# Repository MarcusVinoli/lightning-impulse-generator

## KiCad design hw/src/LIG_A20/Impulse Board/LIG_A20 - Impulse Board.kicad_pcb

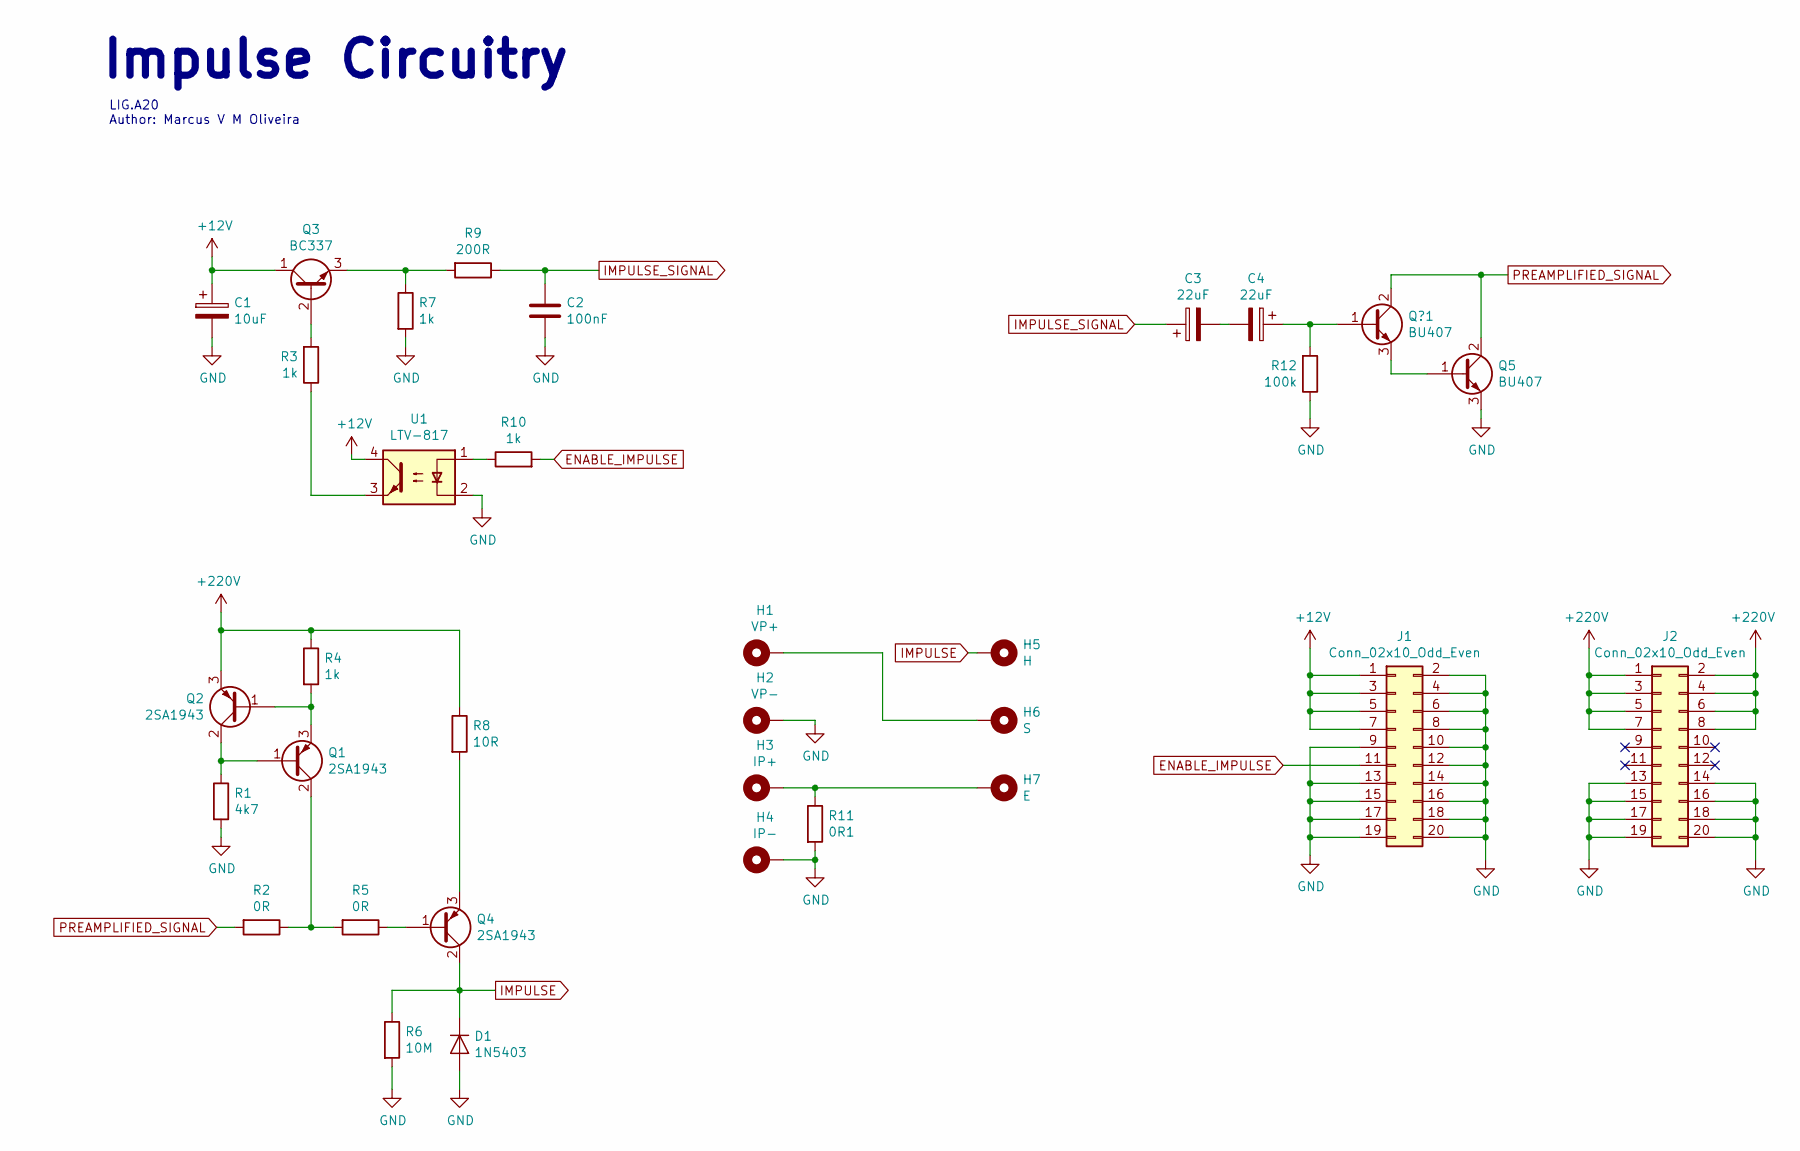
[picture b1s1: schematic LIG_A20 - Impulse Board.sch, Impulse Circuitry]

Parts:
C1: 10uF; CP_Radial_D4.0mm_P2.00mm
C2: 100nF; C_Disc_D5.1mm_W3.2mm_P5.00mm
C3, C4: 22uF; CP_Radial_D4.0mm_P2.00mm
D1: 1N5403; D_DO-201AD_P15.24mm_Horizontal
H1: VP+; MountingHole_2.7mm_M2.5_Pad
H2: VP-; MountingHole_2.7mm_M2.5_Pad
H3: IP+; MountingHole_2.7mm_M2.5_Pad
H4: IP-; MountingHole_2.7mm_M2.5_Pad
H5: H; MountingHole_2.7mm_M2.5_Pad
H6: S; MountingHole_2.7mm_M2.5_Pad
H7: E; MountingHole_2.7mm_M2.5_Pad
J1, J2: Conn_02x10_Odd_Even; PinHeader_2x10_P2.54mm_Vertical
Q1, Q2, Q4: 2SA1943; TO-264-3_Vertical
Q3: BC337; TO-92_Inline
Q5: BU407; TO-220-3_Vertical
Q?1: BU407; TO-220-3_Vertical
R1: 4k7; R_Axial_Power_L38.0mm_W9.0mm_P45.72mm
R2, R5: 0R; R_Axial_DIN0207_L6.3mm_D2.5mm_P10.16mm_Horizontal
R3, R4, R7, R10: 1k; R_Axial_DIN0207_L6.3mm_D2.5mm_P10.16mm_Horizontal
R6: 10M; R_Axial_DIN0207_L6.3mm_D2.5mm_P10.16mm_Horizontal
R8: 10R; R_Axial_Power_L38.0mm_W9.0mm_P45.72mm
R9: 200R; R_Axial_DIN0207_L6.3mm_D2.5mm_P10.16mm_Horizontal
R11: 0R1; R_Axial_DIN0918_L18.0mm_D9.0mm_P25.40mm_Horizontal
R12: 100k; R_Axial_DIN0207_L6.3mm_D2.5mm_P10.16mm_Horizontal
U1: LTV-817; DIP-4_W7.62mm

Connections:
+12V: C1.1, J1.1, J1.3, J1.5, J1.7, Q3.1 (C), U1.4
+220V: J2.1, J2.2, J2.3, J2.4, J2.5, J2.6, J2.7, J2.8, Q2.3 (E), R4.1, R8.1
ENABLE_IMPULSE: J1.11, R10.2
GND: C1.2, C2.2, D1.2 (A), H2.1, H4.1, J1.2, J1.4, J1.6, J1.8, J1.9, J1.10, J1.12, J1.13, J1.14, J1.15, J1.16, J1.17, J1.18, J1.19, J1.20, J2.13, J2.14, J2.15, J2.16, J2.17, J2.18, J2.19, J2.20, Q5.3 (E), R1.2, R6.2, R7.2, R11.2, R12.1, U1.2
IMPULSE: D1.1 (K), H5.1, Q4.2 (C), R6.1
IMPULSE_SIGNAL: C2.1, C3.1, R9.1
unnamed: C3.2, C4.2
unnamed: C4.1, Q?1.1 (B), R12.2
unnamed: H1.1, H6.1
unnamed: H3.1, H7.1, R11.1
unnamed: Q1.1 (B), Q2.2 (C), R1.1
unnamed: Q1.2 (C), R2.1, R5.2
unnamed: Q1.3 (E), Q2.1 (B), R4.2
unnamed: Q3.2 (B), R3.2
unnamed: Q3.3 (E), R7.1, R9.2
unnamed: Q4.1 (B), R5.1
unnamed: Q4.3 (E), R8.2
unnamed: Q5.1 (B), Q?1.3 (E)
unnamed: R3.1, U1.3
unnamed: R10.1, U1.1
PREAMPLIFIED_SIGNAL: Q5.2 (C), Q?1.2 (C), R2.2

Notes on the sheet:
Impulse Circuitry
LIG.A20 Author: Marcus V M Oliveira

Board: 2 copper layers, 33 parts (1 on the bottom side), 21 nets, no tracks yet.

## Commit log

2020-03-19 Commit inicial do Repositório. HV.200319.
